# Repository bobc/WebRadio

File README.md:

# ARM Cortex-M3 WebRadio
The ARM WebRadio is an embedded Internet Radio based on an ARM Cortex-M3 Microcontroller and VS1053 Audio Codec.
The VS1053 can decode various audio formats, including Ogg Vorbis, MP3, AAC, WMA, FLAC, WAV, MIDI.

## Features
* Open-Source Hardware
  * Microcontroller: LM3S6950 ARM Cortex-M3 from Luminary Micro / TI
  * Audio Codec: VS1053 from VLSI
  * Display: S65 LCD with 176x132 pixel and 16bit color
  * microSD Socket
  * Rotary Encoder
  * IR Receiver (RC5)
  * PoE (Power over Ethernet)
* Open-Source Software
  * Play Shoutcast/Icecast and RTSP Streams
  * Play audio files from the memory card
  * Alarm Clock

## Hardware and Software
* 
* [Schematics + Layout](https://github.com/watterott/WebRadio/tree/master/hardware)
* [Software/Firmware](https://github.com/watterott/WebRadio/tree/master/software)

## Videos
* [ARM WebRadio test buildup](http://www.youtube.com/watch?v=d3AU1xSci-s)
* [ARM WebRadio v1 prototype](http://www.youtube.com/watch?v=I5wxE6ul4LM)
* [ARM WebRadio v2 demo board](http://www.youtube.com/watch?v=boI7PvBz0HM)
* [ARM WebRadio v3](http://www.youtube.com/watch?v=70_Qk82P8Xw)

## Notes on this fork

The LM3S6950 is obsolete, there is no equivalent.
The S65 LCD may be hard to find as well.

I converted main and exp boards to KiCad 4.0.2.

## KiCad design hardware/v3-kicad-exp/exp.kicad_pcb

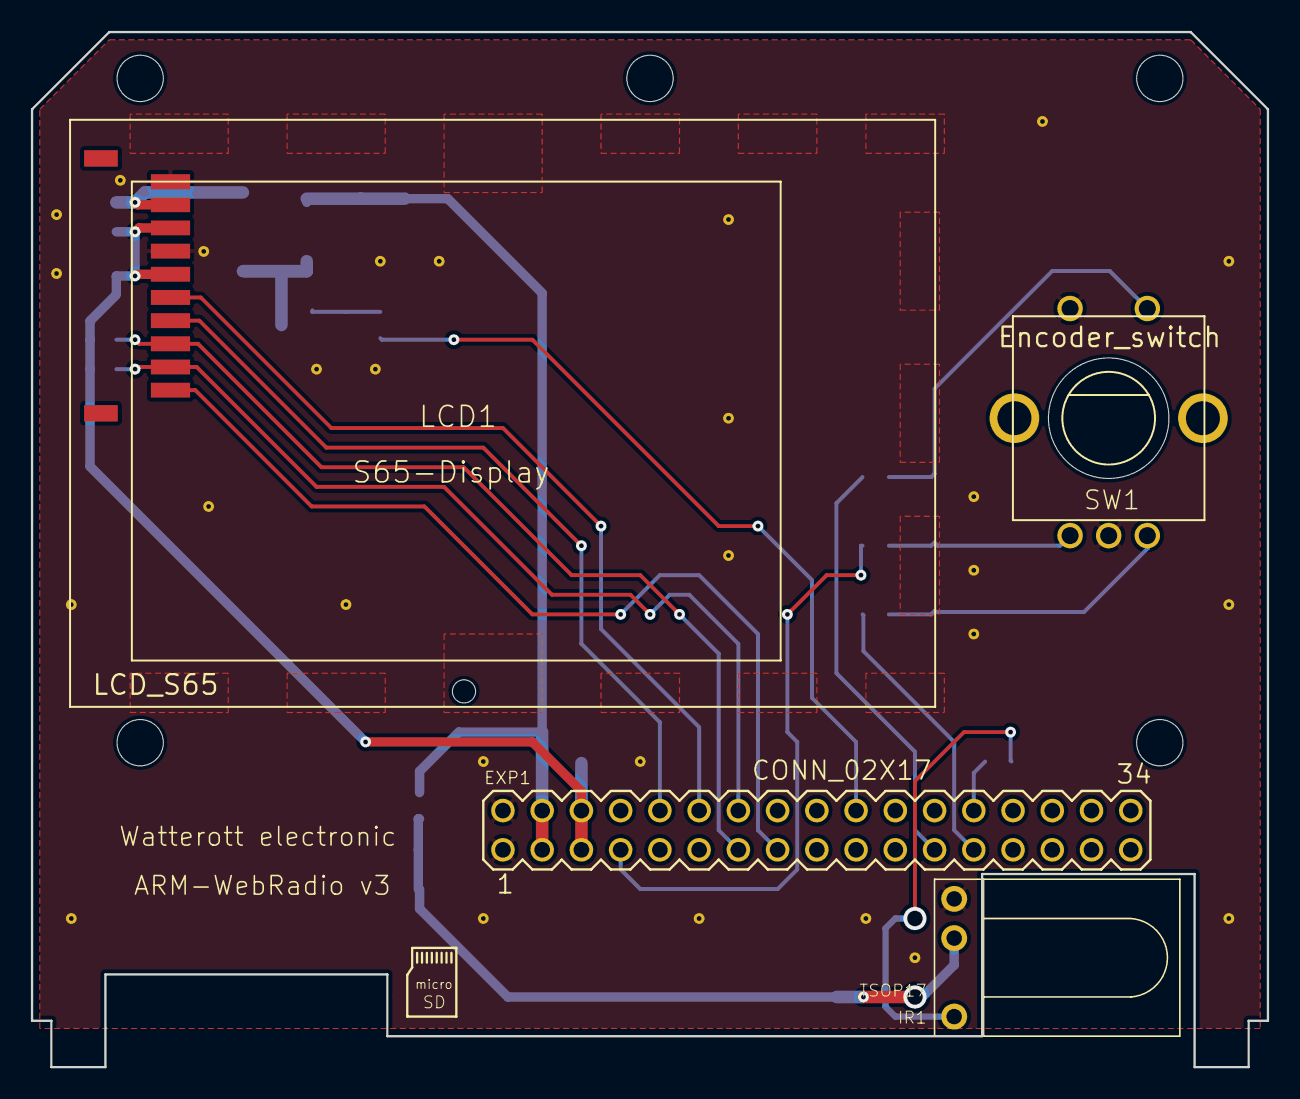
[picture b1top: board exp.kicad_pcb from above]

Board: 2 copper layers, 80.0 x 67.0 mm, 63 parts (0 on the bottom side), 21 nets.

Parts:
@HOLE0, @HOLE1, @HOLE2, @HOLE3, @HOLE4, @HOLE5: HOLE
EXP1: CONN_02X17; MA17-2
EXP_C1, EXP_C2: 100nF; C0603
IR1: TSOP17
IR_C1: 100nF; C0603
IR_C2, IR_C3: 2uF; C0603K
IR_R1: 1k; R0603
IR_R2: 100; R0603
LCD1: LCD_S65; S65
LCD_C1, LCD_C2, LCD_C3, LCD_C4: 100nF; C0603
LCD_C5: 2uF; C0603K
LCD_D1: D; DO214AA
LCD_L1: 1-2mH; 50mA; L4532M
LCD_Q1: Q_NMOS_GSD; MICRO3
LCD_R1, LCD_R2, LCD_R4: 47k; R0603
LCD_R3: 100; R0603
SW1: Encoder_switch; ALPS_EC12E_SW
SW_C1, SW_C2, SW_C3: 2.2nF; C0603
SW_R1, SW_R2, SW_R3: 1k; R0603
V1, V2, V3, V4, V5, V6, V7, V8, V9, V10, V11, V12, V13, V14, V15, V16, V17, V18, V19, V20, V21, V22, V23, V24, V25, V26, V27, V28: via

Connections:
+3V3: EXP1.5, EXP1.6, EXP_C2.1, LCD1.1V8, LCD1.2V9, LCD_C1.1, LCD_C2.1, LCD_R1.2, LCD_R2.2
+5V: EXP1.3, EXP1.4, EXP_C1.1, IR_R2.2, LCD_C4.1, LCD_C5.1, LCD_L1.1
/ENC-A: EXP1.25, SW_R1.2
/ENC-B: EXP1.7, SW_R2.1
/ENC-SW: EXP1.23, SW_R3.2
/IR_RX: EXP1.26, IR_R1.1
/LCD_BACKLIGHT_PWM: EXP1.20, LCD_R3.1
/LCD_CS: EXP1.13, LCD1.CS, LCD_R2.1
/LCD_DATA: EXP1.12, LCD1.DATA
/LCD_RESET: EXP1.14, LCD1.RST, LCD_R1.1
/LCD_RS: EXP1.15, LCD1.RS
/LCD_SCK: EXP1.10, LCD1.CLK
GND: EXP1.1, EXP1.2, EXP_C1.2, EXP_C2.2, IR1.GND, IR_C1.2, IR_C2.2, IR_C3.2, LCD1.GND, LCD1.LED-, LCD_C1.2, LCD_C2.2, LCD_C3.2, LCD_C4.2, LCD_C5.2, LCD_Q1.2, LCD_R4.1, SW1.2, SW1.4, SW_C1.2, SW_C2.2, SW_C3.2, V1.1, V2.1, V3.1, V4.1, V5.1, V6.1, V7.1, V8.1, V9.1, V10.1, V11.1, V12.1, V13.1, V14.1, V15.1, V16.1, V17.1, V18.1, V19.1, V20.1, V21.1, V22.1, V23.1, V24.1, V25.1, V26.1, V27.1, V28.1
unnamed: IR1.VO, IR_R1.2
unnamed: IR1.VS, IR_C1.1, IR_C2.1, IR_C3.1, IR_R2.1
unnamed: LCD1.LED+, LCD_C3.1, LCD_D1.1
unnamed: LCD_D1.2, LCD_L1.2, LCD_Q1.3
unnamed: LCD_Q1.1, LCD_R3.2, LCD_R4.2
unnamed: SW1.1, SW_C1.1, SW_R1.1
unnamed: SW1.3, SW_C2.1, SW_R2.2
unnamed: SW1.5, SW_C3.1, SW_R3.1

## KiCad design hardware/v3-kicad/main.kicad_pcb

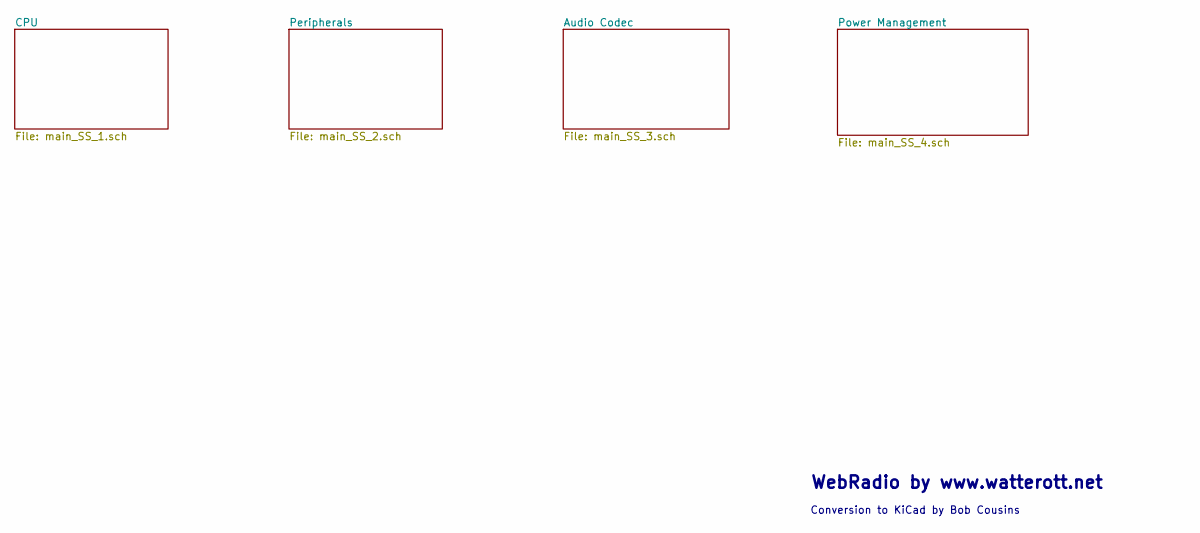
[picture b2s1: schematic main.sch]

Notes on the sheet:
WebRadio by www.watterott.net
Conversion to KiCad by Bob Cousins

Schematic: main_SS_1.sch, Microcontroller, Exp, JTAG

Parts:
ARM37: LM3S6950; LUMINARY_LQFP100
ARM_C1, ARM_C2, ARM_C3, ARM_C4: 18pF; RCL_C0603
ARM_C5, ARM_C6, ARM_C7, ARM_C8, ARM_C9, ARM_C10, ARM_C11, ARM_C12: 100nF; RCL_C0603
ARM_Q1: 8MHz; CRYSTAL_CS10
ARM_Q2: 25MHz; CRYSTAL_CS10
ARM_R1, ARM_R2, ARM_R3: 10k; RCL_R0603
ARM_R4: 12.4k; RCL_R0603
EXP37: CON-LSTB_MA17-2
EXP_C1, EXP_C2: 100nF; RCL_C0603
JTAG37: CON-LST_MA10-2_SMD
R1, R2: 470*; RCL_R0603
UART2: CON-LSTB_MA06-1
X1, X2, X3, X4: SPECIAL-PAD_SMD-ELLIPSE

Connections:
8: ARM37.70 (I2C0SCL/PB2), EXP37.8
13: ARM37.90 (C0+/C0O/PB6), EXP37.13
25: ARM37.11 (PHA0/PD1), EXP37.25
30: ARM37.22 (C2-/PC7), EXP37.30
+3V3: ARM37.3 (VCCA), ARM37.8 (VCC), ARM37.20 (VCC), ARM37.32 (VCC), ARM37.36 (VCCPHY), ARM37.44 (VCC), ARM37.56 (VCC), ARM37.68 (VCC), ARM37.81 (VCC), ARM37.83 (VCCPHY), ARM37.84 (VCCPHY), ARM37.93 (VCC), ARM37.98 (VCCA), ARM_C5.1, ARM_C6.1, ARM_C7.1, ARM_C8.1, ARM_R1.1, ARM_R2.2, ARM_R3.2, EXP37.5, EXP37.6, EXP_C2.2, JTAG37.1; also elsewhere on the board
+5V: EXP37.3, EXP37.4, EXP_C1.2; also elsewhere on the board
/main_SS_1/7: ARM37.47 (PHB0/PF0), EXP37.7
/main_SS_1/9: ARM37.71 (I2C0SDA/PB3), EXP37.9
/main_SS_1/14: ARM37.91 (C1-/PB5), EXP37.14
/main_SS_1/15: ARM37.92 (C0-/PB4), EXP37.15
/main_SS_1/16: ARM37.95 (CCP0/PD4), EXP37.16
/main_SS_1/17: ARM37.96 (CCP2/PD5), EXP37.17
/main_SS_1/18: ARM37.99 (FAULT/PD6), EXP37.18
/main_SS_1/19: ARM37.100 (IDX0/PD7), EXP37.19
/main_SS_1/20: ARM37.1 (PWM5/PE7), EXP37.20
/main_SS_1/21: ARM37.2 (PWM4/PE6), EXP37.21
/main_SS_1/22: ARM37.5 (PE5), EXP37.22
/main_SS_1/23: ARM37.6 (CCP3/PE4), EXP37.23
/main_SS_1/24: ARM37.10 (PWM0/PD0), EXP37.24
/main_SS_1/26: ARM37.12 (U1RX/PD2), EXP37.26
/main_SS_1/27: ARM37.13 (U1TX/PD3), EXP37.27
/main_SS_1/28: ARM37.18 (U2TX/PG1), EXP37.28, R2.1
/main_SS_1/29: ARM37.19 (U2RX/PG0), EXP37.29, R1.1
/main_SS_1/31: ARM37.23 (C2+/C2O/PC6), EXP37.31
/main_SS_1/32: ARM37.24 (C1+/C1O/PC5), EXP37.32
/main_SS_1/33: ARM37.25 (CCP5/PC4), EXP37.33
/main_SS_1/ERBIAS: ARM37.41 (ERBIAS), ARM_R4.1
/main_SS_1/MDIO: ARM37.58 (MDIO), ARM_R3.1
/main_SS_1/N$9: ARM37.48 (OSC0), ARM_C1.1, ARM_Q1.2
/main_SS_1/N$10: ARM37.49 (OSC1), ARM_C2.1, ARM_Q1.1
/main_SS_1/N$13: ARM37.17 (XTALNPHY), ARM_C4.1, ARM_Q2.1
/main_SS_1/N$14: ARM37.16 (XTALPPHY), ARM_C3.1, ARM_Q2.2
/main_SS_1/RESET: ARM37.64 (~RESET), ARM_R1.2
/main_SS_1/RXD: R2.2, UART2.5
/main_SS_1/TCK: ARM37.80 (TCK/SWCLK/PC0), JTAG37.9
/main_SS_1/TDI: ARM37.78 (TDI/PC2), JTAG37.5
/main_SS_1/TDO: ARM37.77 (TDO/SWO/PC3), JTAG37.13
/main_SS_1/TMS: ARM37.79 (TMS/SWDIO/PC1), JTAG37.7
/main_SS_1/TRST: ARM37.89 (TRST/PB7), ARM_R2.1, JTAG37.3
/main_SS_1/TXD: R1.2, UART2.4
FM_CS: ARM37.73 (SSI1FSS/PE1); also elsewhere on the board
GND: ARM37.4 (GNDA), ARM37.9 (GND), ARM37.15 (GND), ARM37.21 (GND), ARM37.33 (GND), ARM37.39 (GND), ARM37.42 (GNDPHY), ARM37.45 (GND), ARM37.50 (~WAKE), ARM37.54 (GND), ARM37.57 (GND), ARM37.63 (GND), ARM37.65 (CMOD0), ARM37.69 (GND), ARM37.76 (CMOD1), ARM37.82 (GND), ARM37.85 (GNDPHY), ARM37.86 (GNDPHY), ARM37.87 (GND), ARM37.94 (GND), ARM37.97 (GNDA), ARM_C1.2, ARM_C2.2, ARM_C3.2, ARM_C4.2, ARM_C5.2, ARM_C6.2, ARM_C7.2, ARM_C8.2, ARM_C9.2, ARM_C10.2, ARM_C11.2, ARM_C12.2, ARM_R4.2, EXP37.1, EXP37.2, EXP_C1.1, EXP_C2.1, JTAG37.4, JTAG37.6, JTAG37.8, JTAG37.10, JTAG37.12, JTAG37.14, JTAG37.16, JTAG37.18, JTAG37.20, UART2.1; also elsewhere on the board
LED1: ARM37.59 (LED0/PF3); also elsewhere on the board
LED2: ARM37.60 (LED1/PF2); also elsewhere on the board
RD+: ARM37.40 (RXIP); also elsewhere on the board
RD-: ARM37.37 (RXIN); also elsewhere on the board
SCK: ARM37.72 (SSI1CLK/PE0), EXP37.10; also elsewhere on the board
SD_CS: ARM37.67 (PWM3/PB1); also elsewhere on the board
SD_PWR: ARM37.66 (PWM2/PB0); also elsewhere on the board
SI: ARM37.75 (SSI1TX/PE3), EXP37.12; also elsewhere on the board
SO: ARM37.74 (SSI1RX/PE2), EXP37.11; also elsewhere on the board
TD+: ARM37.43 (TXOP); also elsewhere on the board
TD-: ARM37.46 (TXON); also elsewhere on the board
USB_PWR: ARM37.61 (PWM1/PF1); also elsewhere on the board
VCCIO: ARM37.7 (LDO), ARM37.14 (VCC25), ARM37.38 (VCC25), ARM37.62 (VCC25), ARM37.88 (VCC25), ARM_C9.1, ARM_C10.1, ARM_C11.1, ARM_C12.1
VS_CS: ARM37.34 (CCP1/PA6); also elsewhere on the board
VS_DCS: ARM37.29 (SSI0FSS/PA3); also elsewhere on the board
VS_DREQ: ARM37.27 (U0TX/PA1); also elsewhere on the board
VS_RST: ARM37.35 (CCP4/PA7); also elsewhere on the board
VS_SCK: ARM37.28 (SSI0CLK/PA2); also elsewhere on the board
VS_SI: ARM37.31 (SSI0TX/PA5); also elsewhere on the board
VS_SO: ARM37.30 (SSI0RX/PA4); also elsewhere on the board

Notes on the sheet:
CTS
3V3
GND
TxD
RxD
DTR
FTDI Basic Breakout

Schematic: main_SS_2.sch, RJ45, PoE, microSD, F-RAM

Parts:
FM37: FM25V...; RAMTRON_SO8
FM_C1: 100nF; RCL_C0603
FM_R1: 47k; RCL_R0603
POE37: TPS2375D; ETHERNET_SO08
POE_C1: 100nF; RCL_C1206
POE_CLA37: 4,3k; RCL_R0603
POE_D1: SMAJ58A; DIODE_DO214AA
POE_DET37: 24k; RCL_R0603
POE_ILM37: 100k; RCL_R0603
RJ37: RJ45-8-POEWE; ETHERNET_WE_POE
RJ_C1: 100nF; RCL_C0603
RJ_C2, RJ_C5, RJ_C6, RJ_C9: 10pF; RCL_C0603
RJ_C3, RJ_C4, RJ_C7, RJ_C8, RJ_C10: 10nF; RCL_C0603
RJ_R1, RJ_R2, RJ_R3, RJ_R4: 50; RCL_R0603
RJ_R5, RJ_R6: 470; RCL_R0603
RJ_R7: 100; RCL_R0603
SD37: MICRO-SD; SD-CARD_MICRO-SD
SD_C1, SD_C2: 100nF; RCL_C0603
SD_C3: 2uF; RCL_C0603
SD_Q1: P-CHN; IRF-SOT23_MICRO3
SD_R1, SD_R2, SD_R3, SD_R4, SD_R5: 47k; RCL_R0603

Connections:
+3V3: FM37.3 (-WP), FM37.7 (-HOLD), FM37.8 (VCC), FM_C1.1, FM_R1.2, RJ37.3 (RCT), RJ37.4 (TCT), RJ37.L1_P (LED1+), RJ37.L2_P (LED2+), RJ_C1.1, RJ_C3.2, RJ_C4.2, RJ_C7.2, RJ_C8.2, RJ_R1.2, RJ_R2.2, RJ_R3.2, RJ_R4.2, SD_C2.2, SD_C3.2, SD_Q1.2 (S), SD_R1.1; also elsewhere on the board
/main_SS_2/CLASS: POE37.2 (CLASS), POE_CLA37.2
/main_SS_2/DET: POE37.3 (DET), POE_DET37.2
/main_SS_2/ILM: POE37.1 (ILM), POE_ILM37.2
/main_SS_2/N$4: RJ37.L2_N (LED2-), RJ_R6.1
/main_SS_2/N$5: RJ37.L1_N (LED1-), RJ_R5.1
/main_SS_2/N$29: RJ_C10.1, RJ_R7.1
/main_SS_2/POE-: POE37.4 (POE-), POE_C1.2, POE_CLA37.1, POE_D1.A, POE_ILM37.1, RJ37.10 (POE-)
/main_SS_2/SD_1: SD37.1, SD_R5.2
/main_SS_2/SD_3V3: SD37.4, SD_C1.1, SD_Q1.3 (D), SD_R2.1, SD_R3.1, SD_R4.1, SD_R5.1
/main_SS_2/SD_8: SD37.8, SD_R2.2
/main_SS_2/SHIELD: RJ37.NC0 (SHIELD), RJ37.NC1 (SHIELD), RJ_R7.2
FM_CS: FM37.1 (-CS), FM_R1.1; also elsewhere on the board
GND: FM37.4 (GND), FM_C1.2, POE37.5 (RTN), RJ_C1.2, RJ_C2.1, RJ_C3.1, RJ_C4.1, RJ_C5.1, RJ_C6.1, RJ_C7.1, RJ_C8.1, RJ_C9.1, RJ_C10.2, SD37.6, SD_C1.2, SD_C2.1, SD_C3.1; also elsewhere on the board
LED1: RJ_R5.2; also elsewhere on the board
LED2: RJ_R6.2; also elsewhere on the board
POE+: RJ37.9 (POE+); also elsewhere on the board
PWR+: POE37.8 (POE+), POE_C1.1, POE_D1.C, POE_DET37.1; also elsewhere on the board
RD+: RJ37.1 (RD+), RJ_C2.2, RJ_R1.1; also elsewhere on the board
RD-: RJ37.2 (RD-), RJ_C5.2, RJ_R2.1; also elsewhere on the board
SCK: FM37.6 (CLK), SD37.5; also elsewhere on the board
SD_CS: SD37.2, SD_R4.2; also elsewhere on the board
SD_PWR: SD_Q1.1 (G), SD_R1.2; also elsewhere on the board
SI: FM37.5 (DI), SD37.3; also elsewhere on the board
SO: FM37.2 (DO), SD37.7, SD_R3.2; also elsewhere on the board
TD+: RJ37.5 (TD+), RJ_C6.2, RJ_R3.1; also elsewhere on the board
TD-: RJ37.6 (TD-), RJ_C9.2, RJ_R4.1; also elsewhere on the board

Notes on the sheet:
RJ45 + PoE
F-RAM (optional)
4k4
100k
25k
microSD

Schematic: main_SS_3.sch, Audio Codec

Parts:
I2S37: CON-LSTB_MA04-1
OUT37: 1503_09; AUDIO_1503_09
PWR37: CON-LSTB_MA04-1
PWR_C1, PWR_C2: 100nF; RCL_C0603
VS37: VS1053; VLSI_LQFP-48
VS_C1, VS_C2: 27pF; RCL_C0603
VS_C3, VS_C4: 10nF; RCL_C0603
VS_C5: 47nF; RCL_C0603
VS_C6: 1uF; RCL_C0603
VS_C7, VS_C8, VS_C9, VS_C10, VS_C11, VS_C12, VS_C13, VS_C14, VS_C15: 100nF; RCL_C0603
VS_CL2: 2.2nF; RCL_C0603
VS_CL37: 10uF; RCL_C1210
VS_CR2: 2.2nF; RCL_C0603
VS_CR37: 10uF; RCL_C1210
VS_GBUF37: 0*; RCL_R0603
VS_GND37: 0*; RCL_R0603
VS_Q1: 12.288MHz; CRYSTAL_SM49
VS_R1: 1M; RCL_R0603
VS_R2, VS_R3, VS_R9, VS_R10, VS_R11, VS_R12: 100k; RCL_R0603
VS_R4, VS_R5: 22; RCL_R0603
VS_R6: 10; RCL_R0603
VS_R7, VS_R8: 10k; RCL_R0603
VS_RL37: 470; RCL_R0603
VS_RR37: 470; RCL_R0603

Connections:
+1V8: VS37.5 (CVCC0), VS37.7 (CVCC1), VS37.24 (CVCC2), VS37.31 (CVCC3), VS_C10.1, VS_C11.1, VS_C12.1, VS_C13.1; also elsewhere on the board
+2V8: VS37.38 (AVCC0), VS37.43 (AVCC1), VS37.45 (AVCC2), VS_C14.1, VS_C15.1; also elsewhere on the board
+3V3: PWR37.2, PWR_C1.2, VS37.6 (IOVCC0), VS37.14 (IOVCC1), VS37.19 (IOVCC2), VS37.26 (RX), VS37.32 (TEST), VS_C7.1, VS_C8.1, VS_C9.1; also elsewhere on the board
+5V: PWR37.1, PWR_C2.2; also elsewhere on the board
/main_SS_3/GBUF: VS37.42 (GBUF), VS_GBUF37.1, VS_R6.2
/main_SS_3/I2S_LROUT: I2S37.1, VS37.36 (GPIO4), VS_R9.1
/main_SS_3/I2S_MCLK: I2S37.2, VS37.25 (GPIO5), VS_R10.1
/main_SS_3/I2S_SCLK: I2S37.3, VS37.11 (GPIO6), VS_R11.1
/main_SS_3/I2S_SDATA: I2S37.4, VS37.12 (GPIO7), VS_R12.1
/main_SS_3/LEFT: VS37.46 (LEFT), VS_R4.2, VS_RL37.1
/main_SS_3/N$3: VS37.33 (GPIO0), VS37.34 (GPIO1), VS_R3.2
/main_SS_3/N$6: VS37.9 (GPIO2), VS37.10 (GPIO3), VS_R2.2
/main_SS_3/N$8: VS37.18 (XTALI), VS_C2.1, VS_Q1.1, VS_R1.2
/main_SS_3/N$11: VS37.17 (XTALO), VS_C1.1, VS_Q1.2, VS_R1.1
/main_SS_3/N$18: OUT37.1, VS_GBUF37.2, VS_GND37.1
/main_SS_3/N$19: OUT37.3, OUT37.5, VS_CR37.2, VS_R7.1
/main_SS_3/N$20: OUT37.2, OUT37.4, VS_CL37.2, VS_R8.1
/main_SS_3/N$21: VS_CR2.1, VS_CR37.1, VS_RR37.2
/main_SS_3/N$22: VS_CL2.1, VS_CL37.1, VS_RL37.2
/main_SS_3/N$31: VS_C3.2, VS_R4.1
/main_SS_3/N$32: VS_C4.2, VS_R5.1
/main_SS_3/N$33: VS_C5.2, VS_R6.1
/main_SS_3/RCAP: VS37.44 (RCAP), VS_C6.2
/main_SS_3/RIGHT: VS37.39 (RIGHT), VS_R5.2, VS_RR37.1
AGND: VS37.37 (AGND0), VS37.40 (AGND1), VS37.41 (AGND2), VS37.47 (AGND3), VS_C3.1, VS_C4.1, VS_C5.1, VS_C6.1, VS_C14.2, VS_C15.2, VS_CL2.2, VS_CR2.2, VS_GND37.2, VS_R7.2, VS_R8.2; also elsewhere on the board
GND: PWR37.3, PWR37.4, PWR_C1.1, PWR_C2.1, VS37.4 (GND0), VS37.16 (GND1), VS37.20 (GND2), VS37.21 (GND3), VS37.22 (GND4), VS37.35 (GND5), VS_C1.2, VS_C2.2, VS_C7.2, VS_C8.2, VS_C9.2, VS_C10.2, VS_C11.2, VS_C12.2, VS_C13.2, VS_R2.1, VS_R3.1, VS_R9.2, VS_R10.2, VS_R11.2, VS_R12.2; also elsewhere on the board
VS_CS: VS37.23 (~CS); also elsewhere on the board
VS_DCS: VS37.13 (~DCS); also elsewhere on the board
VS_DREQ: VS37.8 (~DREQ); also elsewhere on the board
VS_RST: VS37.3 (~RESET); also elsewhere on the board
VS_SCK: VS37.28 (SCLK); also elsewhere on the board
VS_SI: VS37.29 (SI); also elsewhere on the board
VS_SO: VS37.30 (SO); also elsewhere on the board

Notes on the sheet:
Normal Line-Out
Line-Out for Headphones
VS_GND
VS_GBUF
VS_RR
VS_RL
VS_CL
VS_CR
not mounted
470
10uF
shorted
VS_CR2
VS_CL2
2.2nF
Note: For VS1033 U4 has to be a 2.5V regulator.
Line-Out = green
(Dont use with USB powered speakers)
Further Infos: VLSI AppNote: Connecting analog outputs
GND-AGND

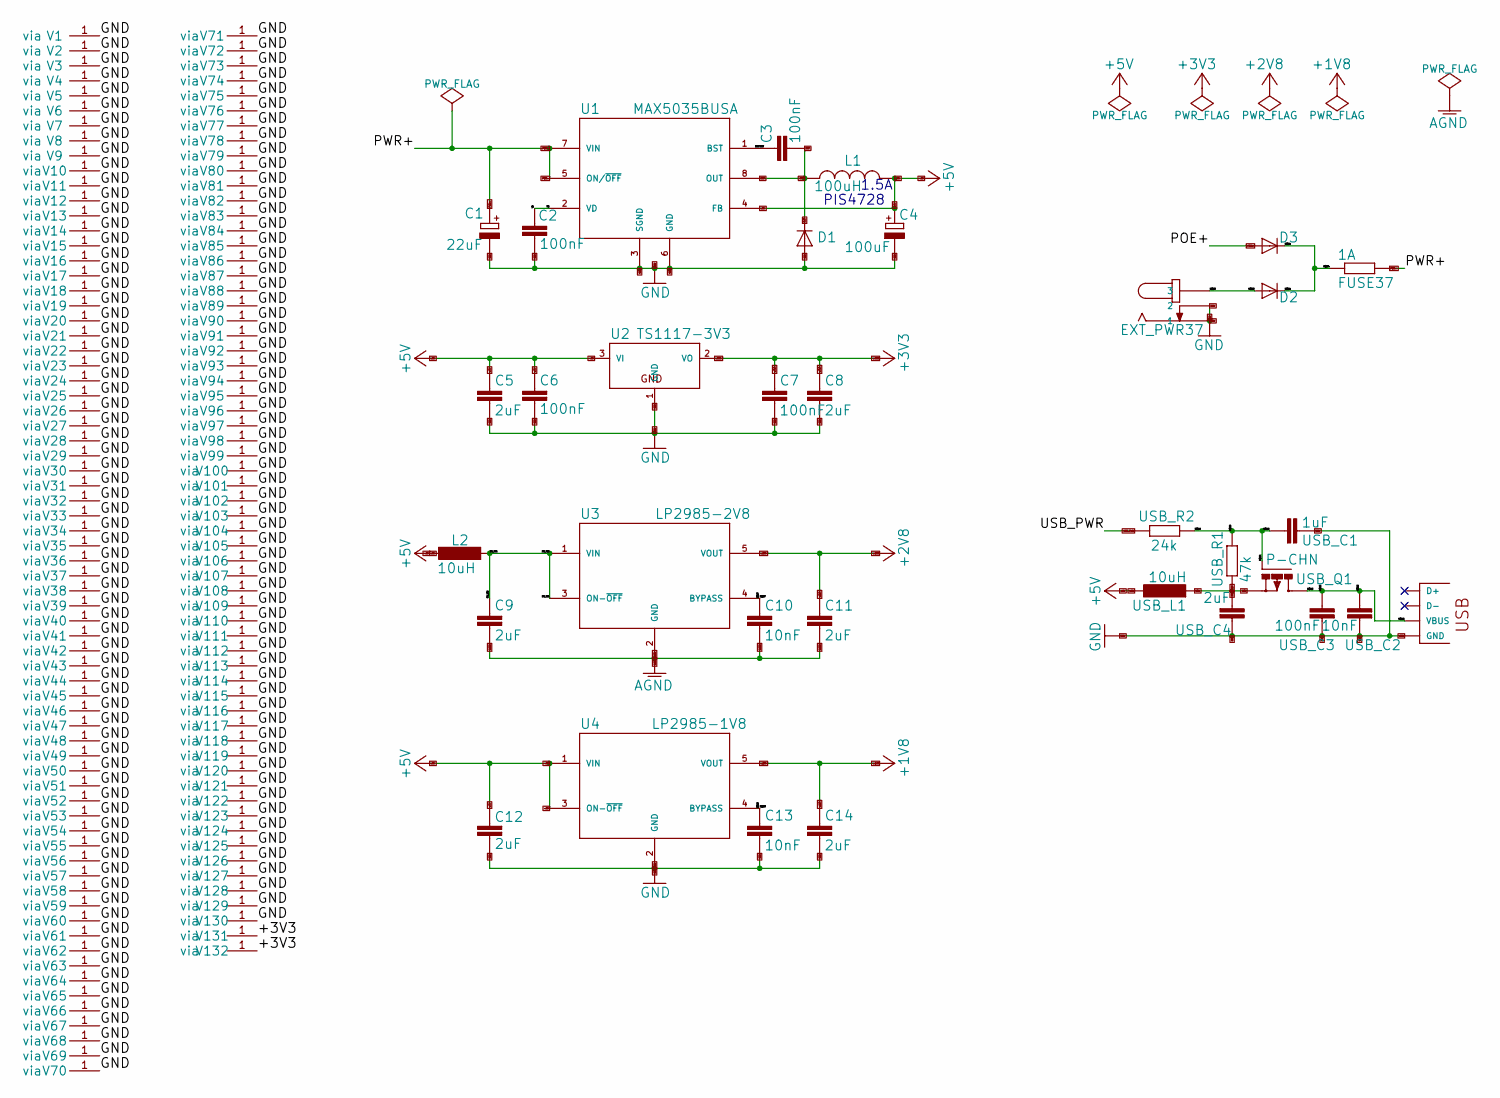
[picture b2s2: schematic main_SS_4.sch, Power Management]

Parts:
C1: 22uF; RCL_153CLV-0810
C2, C3, C6, C7: 100nF; RCL_C0603
C4: 100uF; RCL_153CLV-0810
C5, C8, C9, C11, C12, C14: 2uF; RCL_C0603
C10, C13: 10nF; RCL_C0603
D1, D2, D3: DIODE_DO214AA
EXT_PWR37: CON-JACK_SPC4077
FUSE37: 1A; RCL_R1206
L1: 100uH; VOLTAGE-REG_CDRH
L2: 10uH; RCL_L3230M
U1: MAX5035BUSA; VOLTAGE-REG_SO8
U2: TS1117-3V3; VOLTAGE-REG_SOT223
U3: LP2985-2V8; VOLTAGE-REG_SOT23-5
U4: LP2985-1V8; VOLTAGE-REG_SOT23-5
USB37: USB-A-S; CON-USB_USB-A-S
USB_C1: 1uF; RCL_C0603
USB_C2: 10nF; RCL_C0603
USB_C3: 100nF; RCL_C0603
USB_C4: 2uF; RCL_C0805
USB_L1: 10uH; RCL_L3230M
USB_Q1: P-CHN; IRF-SOT23_MICRO3
USB_R1: 47k; RCL_R0603
USB_R2: 24k; RCL_R0603
V1, V2, V3, V4, V5, V6, V7, V8, V9, V10, V11, V12, V13, V14, V15, V16, V17, V18, V19, V20, V21, V22, V23, V24, V25, V26, V27, V28, V29, V30, V31, V32, V33, V34, V35, V36, V37, V38, V39, V40, V41, V42, V43, V44, V45, V46, V47, V48, V49, V50, V51, V52, V53, V54, V55, V56, V57, V58, V59, V60, V61, V62, V63, V64, V65, V66, V67, V68, V69, V70, V71, V72, V73, V74, V75, V76, V77, V78, V79, V80, V81, V82, V83, V84, V85, V86, V87, V88, V89, V90, V91, V92, V93, V94, V95, V96, V97, V98, V99, V100, V101, V102, V103, V104, V105, V106, V107, V108, V109, V110, V111, V112, V113, V114, V115, V116, V117, V118, V119, V120, V121, V122, V123, V124, V125, V126, V127, V128, V129, V130, V131, V132: via

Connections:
+1V8: C14.1, U4.5 (VOUT); also elsewhere on the board
+2V8: C11.1, U3.5 (VOUT); also elsewhere on the board
+3V3: C7.1, C8.1, U2.2 (VO), V131.1, V132.1; also elsewhere on the board
+5V: C4.+, C5.1, C6.2, C12.2, L1.2, L2.1, U1.4 (FB), U2.3 (VI), U4.1 (VIN), U4.3 (ON-~OFF), USB_L1.1; also elsewhere on the board
/main_SS_4/5V_VIN: C9.2, L2.2, U3.1 (VIN), U3.3 (ON-~OFF)
/main_SS_4/BST: C3.1, U1.1 (BST)
/main_SS_4/N$12: USB37.VBUS, USB_C2.1, USB_C3.1, USB_Q1.3 (D)
/main_SS_4/N$16: USB_C1.2, USB_Q1.1 (G), USB_R1.2, USB_R2.1
/main_SS_4/N$23: D2.A, EXT_PWR37.3
/main_SS_4/N$24: D2.C, D3.C, FUSE37.1
/main_SS_4/N$27: C10.1, U3.4 (BYPASS)
/main_SS_4/N$28: C13.1, U4.4 (BYPASS)
/main_SS_4/VD: C2.1, U1.2 (VD)
AGND: C9.1, C10.2, C11.2, U3.2 (GND); also elsewhere on the board
GND: C1.-, C2.2, C4.-, C5.2, C6.1, C7.2, C8.2, C12.1, C13.2, C14.2, D1.A, EXT_PWR37.1, EXT_PWR37.2, U1.3 (SGND), U1.6 (GND), U2.1 (GND), U4.2 (GND), USB37.GND, USB_C1.1, USB_C2.2, USB_C3.2, USB_C4.1, V1.1, V2.1, V3.1, V4.1, V5.1, V6.1, V7.1, V8.1, V9.1, V10.1, V11.1, V12.1, V13.1, V14.1, V15.1, V16.1, V17.1, V18.1, V19.1, V20.1, V21.1, V22.1, V23.1, V24.1, V25.1, V26.1, V27.1, V28.1, V29.1, V30.1, V31.1, V32.1, V33.1, V34.1, V35.1, V36.1, V37.1, V38.1, V39.1, V40.1, V41.1, V42.1, V43.1, V44.1, V45.1, V46.1, V47.1, V48.1, V49.1, V50.1, V51.1, V52.1, V53.1, V54.1, V55.1, V56.1, V57.1, V58.1, V59.1, V60.1, V61.1, V62.1, V63.1, V64.1, V65.1, V66.1, V67.1, V68.1, V69.1, V70.1, V71.1, V72.1, V73.1, V74.1, V75.1, V76.1, V77.1, V78.1, V79.1, V80.1, V81.1, V82.1, V83.1, V84.1, V85.1, V86.1, V87.1, V88.1, V89.1, V90.1, V91.1, V92.1, V93.1, V94.1, V95.1, V96.1, V97.1, V98.1, V99.1, V100.1, V101.1, V102.1, V103.1, V104.1, V105.1, V106.1, V107.1, V108.1, V109.1, V110.1, V111.1, V112.1, V113.1, V114.1, V115.1, V116.1, V117.1, V118.1, V119.1, V120.1, V121.1, V122.1, V123.1, V124.1, V125.1, V126.1, V127.1, V128.1, V129.1, V130.1; also elsewhere on the board
unnamed: USB_C4.2, USB_L1.2, USB_Q1.2 (S), USB_R1.1
OUT: C3.2, D1.C, L1.1, U1.8 (OUT)
POE+: D3.A; also elsewhere on the board
PWR+: C1.+, FUSE37.2, U1.5 (ON/~OFF), U1.7 (VIN); also elsewhere on the board
USB_PWR: USB_R2.2; also elsewhere on the board

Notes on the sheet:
1.5A
PIS4728

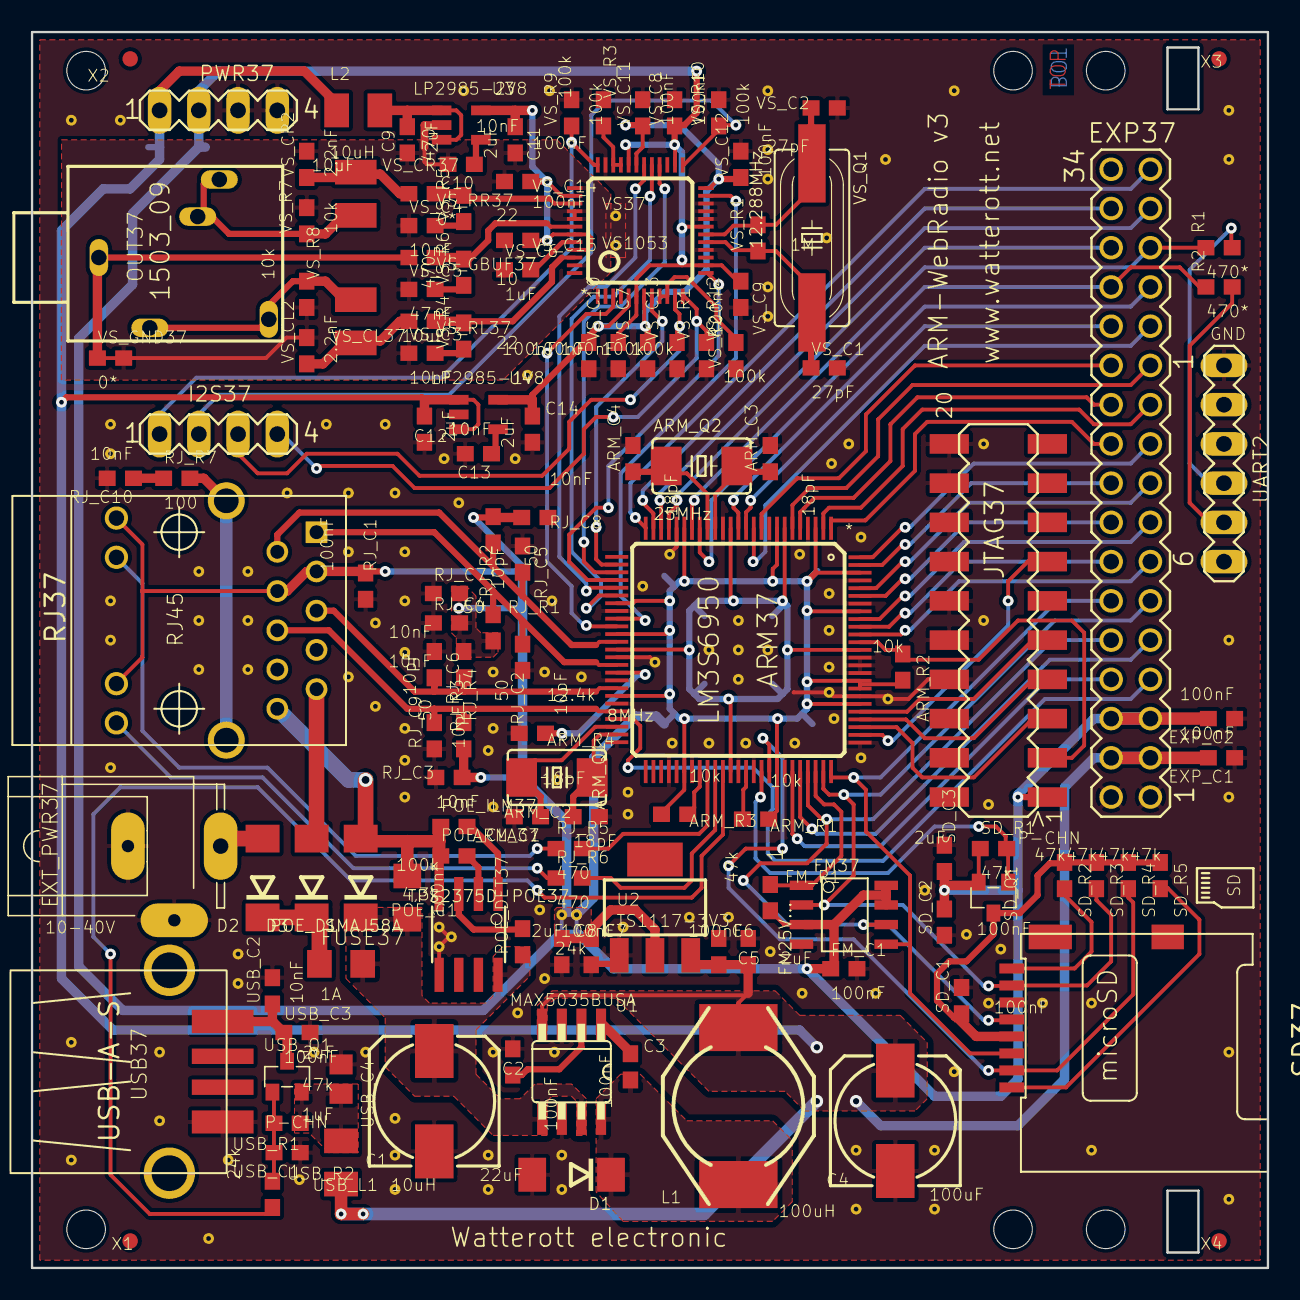
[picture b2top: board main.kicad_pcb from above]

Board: 2 copper layers, 80.0 x 80.0 mm, 281 parts (0 on the bottom side), 109 nets.

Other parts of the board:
@HOLE0, @HOLE1, @HOLE2, @HOLE3, @HOLE4, @HOLE5: (no value)

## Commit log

2017-01-17 KiCad conversion of main board.
2017-01-17 KiCad conversion of display board (exp).
2017-01-25 Save "main" project in Eagle XML format
